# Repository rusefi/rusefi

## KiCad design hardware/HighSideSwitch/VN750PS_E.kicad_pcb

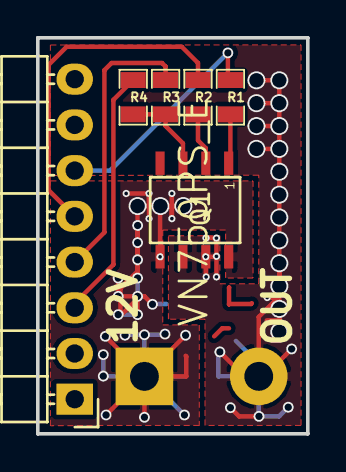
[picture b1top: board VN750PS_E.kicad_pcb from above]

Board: 4 copper layers, 15.0 x 22.0 mm, 8 parts (1 on the bottom side), 9 nets.

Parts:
D1: D; SM0805-diode
P1: CONN_01X08; Pin_Header_Angled_1x08
P2: CONN_01X02; Pin_Header_Straight_25x02
Q1: VN750PS_E; VN750PS-E
R1: 130; RES_0805
R2, R3, R4: 10k; RES_0805

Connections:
+5V: P1.3, R4.1
+12V: D1.1, P2.1, Q1.5, Q1.8
GND: P1.6, R1.1
unnamed: D1.2, P2.2, Q1.6, Q1.7
unnamed: P1.4, R3.1
unnamed: P1.5, R2.1
unnamed: Q1.1, R1.2
unnamed: Q1.2, R2.2
unnamed: Q1.3, R3.2, R4.2

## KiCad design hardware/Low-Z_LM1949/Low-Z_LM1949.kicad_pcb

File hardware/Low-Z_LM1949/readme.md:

https://rusefi.com/forum/viewtopic.php?f=4&t=431

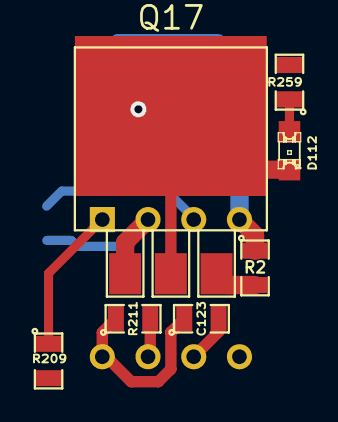
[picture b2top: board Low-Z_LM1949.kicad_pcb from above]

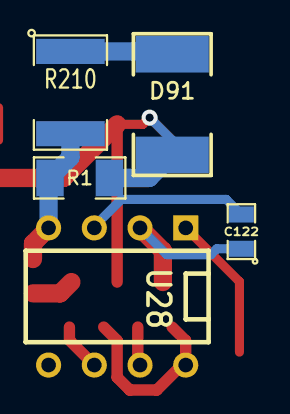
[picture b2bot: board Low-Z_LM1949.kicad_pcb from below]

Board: 2 copper layers, 12 parts (5 on the bottom side), 11 nets.

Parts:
C122: .01uF; SM0805
C123: 0.1uF; SM0805
D91: 33v 5w; SM2512
D112: LED; LED-0805
Q17: 2N6045; DPAK3
R1: 3.9k 1W; SM1206
R2: 2R; SM0805
R209: 1k; SM0805
R210: 0.1 2W; SM1812
R211: 39k; SM0805
R259: 3.3k; SM0805
U28: LM1949; DIP-8__300

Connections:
/5v_reg: R211.2, U28.7
/inductive_power_gnd: D91.1, R210.1, U28.5
/injector_output: D91.2, D112.2, Q17.2, R1.1
GND: C123.2, U28.6
unnamed: C122.1, Q17.1, U28.2
unnamed: C122.2, U28.3
unnamed: C123.1, R211.1, U28.8
unnamed: D112.1, R259.1
unnamed: Q17.3, R2.1, R210.2
unnamed: R1.2, R2.2, U28.4
unnamed: R209.1, U28.1

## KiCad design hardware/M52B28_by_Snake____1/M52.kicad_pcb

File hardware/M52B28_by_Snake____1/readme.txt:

https://rusefi.com/forum/viewtopic.php?f=3&t=1099

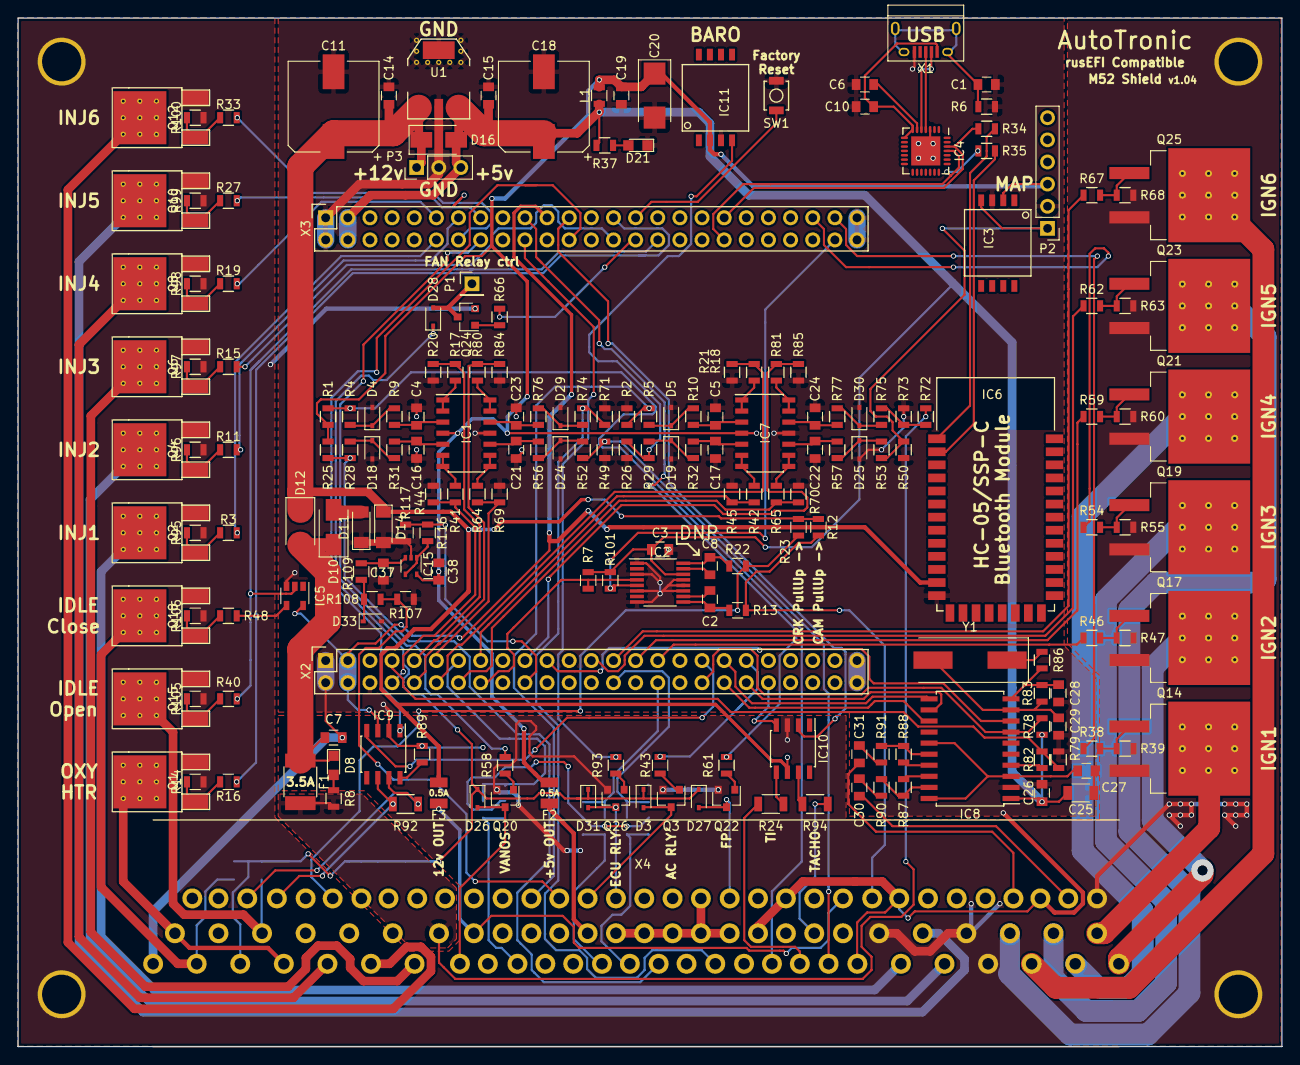
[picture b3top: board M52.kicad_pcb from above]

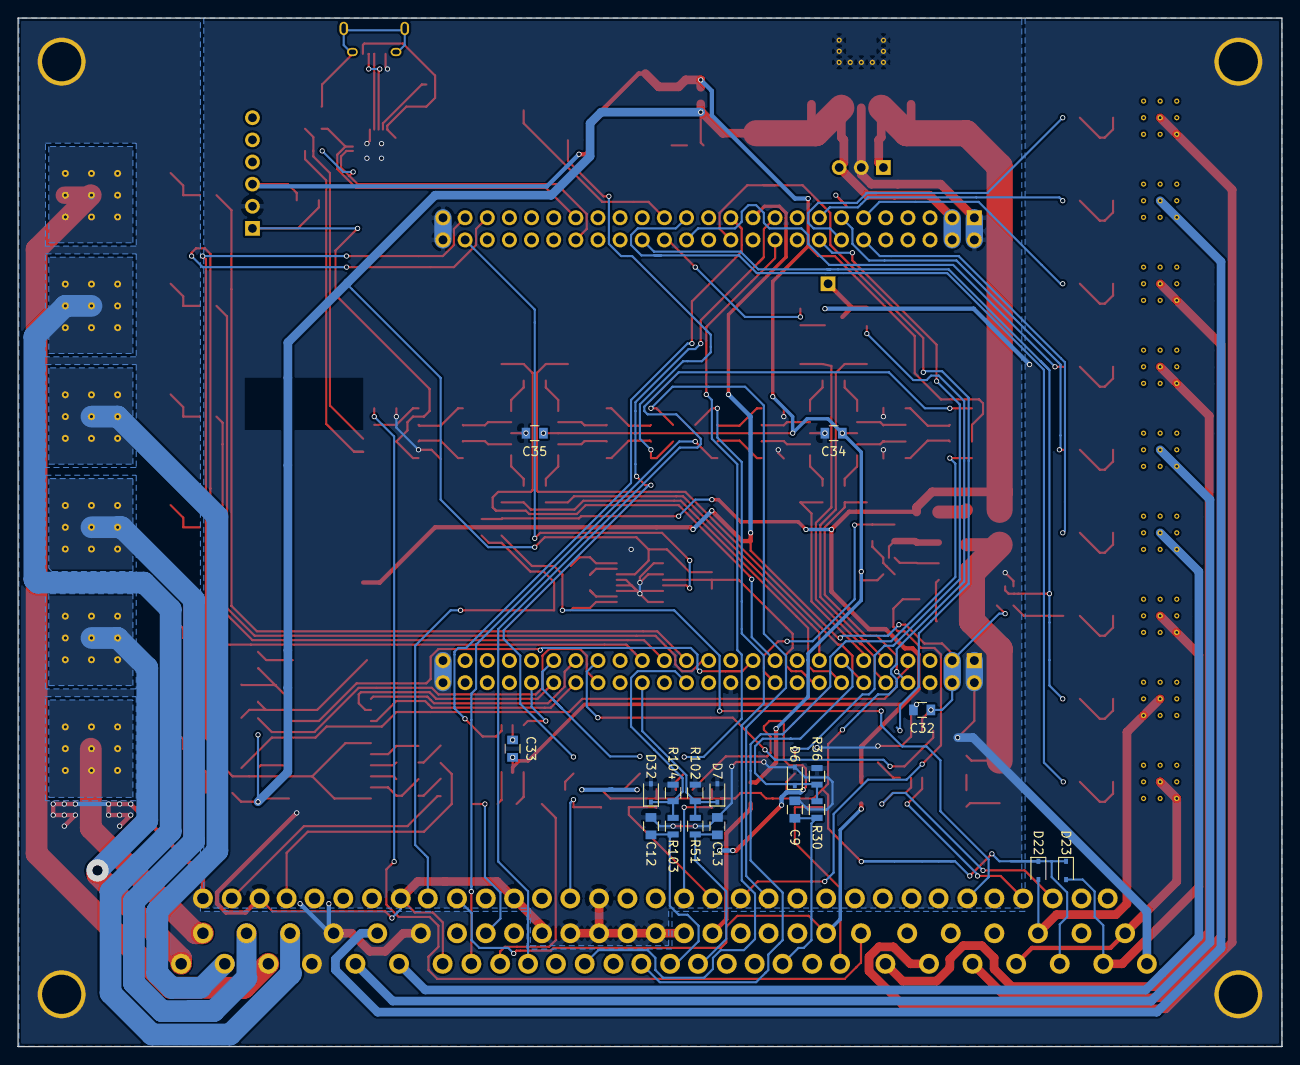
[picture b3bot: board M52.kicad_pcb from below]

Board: 2 copper layers, 145.0 x 118.0 mm, 220 parts (18 on the bottom side), 173 nets.

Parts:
C1, C3, C6, C10, C14, C15, C19, C26, C32, C33, C34, C35, C38: 100nF; C_0805
C2, C7, C8, C9: 1nF; C_0805
C4, C5, C12, C13, C16, C17, C21, C22, C23, C24, C37: 10nF; C_0805
C11, C18: 470uF; CP_Elec_10x10
C20: 10uF; CP_Tantalum_Case-C_EIA-6032-28_Reflow
C25: 4.7uF; C_1206
C27: 220nF; C_0805
C28, C29: 24pF; C_0805
C30, C31: 3.3nF; C_0805
D3, D22, D23, D26, D27, D28, D31: LL4148; D_SOD-323
D4, D5, D18, D19, D24, D25, D29, D30, D33: 5.1v; D_SOD-323
D6, D7, D32: 3.3v; D_SOD-323
D8: RED; LED_0805
D10, D16: LL4007; D_SMA_Standard
D11: 12v; D_MiniMELF
D12: SS34; D_SMA_Standard
D14: 22v; D_MiniMELF
D21: GREEN; LED_0805
F1: 3.5A; R_1812
F2, F3: 500mA; Fuse_SMD1206_Reflow
IC1, IC7: MCP6004; SOIC-14_3.9x8.7mm_Pitch1.27mm
IC2: MAX9926; QSOP-16_3.9x4.9mm_Pitch0.635mm
IC3, IC11: MPXH6400; MPXH6xxx
IC4: CP21xx; QFN-28-1EP_5x5mm_Pitch0.5mm
IC5: 74AHC1G14; SOT-23-5
IC6: HC-05
IC8: TPIC8101; SOIC-20W_7.5x12.8mm_Pitch1.27mm
IC9: SN65HVD230; SOIC-8_3.9x4.9mm_Pitch1.27mm
IC10: IX4424; SOIC-8_3.9x4.9mm_Pitch1.27mm
IC15: MCP6001; SOT-353_SC-70-5
L1: 1uH; R_0805
P1: FAN; Pin_Header_Straight_1x01_Pitch2.54mm
P2: MAP; Pin_Header_Straight_1x06_Pitch2.54mm
P3: CONN_01X03; Pin_Header_Straight_1x03_Pitch2.54mm
Q1, Q2, Q4, Q6, Q8, Q10, Q12, Q15, Q18: IRLR3103
Q3, Q20, Q22, Q24, Q26: MMBT2222A; SOT-23
Q14, Q17, Q19, Q21, Q23, Q25: NGD8201; TO-263-3LeadThermal
R1, R25, R30, R51, R103: 2.7K; R_0805
R2, R26, R49, R50, R71, R107: 500K; R_0805
R3, R11, R15, R16, R19, R27, R33, R34, R35, R36, R38, R40, R43, R46, R48, R54, R58, R59, R61, R62, R66, R67, R93, R102, R104: 1K; R_0805
R4, R5, R7, R8, R13, R22, R28, R29, R37, R52, R53, R73, R74, R75, R79, R82, R89, R101, R108: 10K; R_0805
R6, R14, R39, R47, R55, R60, R63, R68, R95, R96, R97, R98, R99, R100, R105, R106: 100K; R_0805
R9, R10, R31, R32, R56, R57, R76, R77, R109: 100R; R_0805
R12, R23: 4.7K; R_0805
R17, R18, R20, R21, R41, R42, R44, R45, R64, R65, R69, R70, R80, R81, R84, R85, R116, R117: 1.5K; R_0805
R24, R94: 22R; R_1206
R72: 50K; R_0805
R78: 5K; R_0805
R83: 2M; R_0805
R86: 820R; R_0805
R87, R88, R90, R91: 39K; R_0805
R92: 120R; R_1206
SW1: SW_Push; SW_SPST_B3U-1000P
U1: LM340MP-5.0; SOT-223Th.Relief
X1: USB_OTG; USB_Micro-B
X2, X3: CONN_02X25; Socket_Strip_Straight_2x25
X4: BOSCH_88PIN_02X44; BOSCH-88pin
Y1: 8MHz; Crystal_SMD_HC49-SD

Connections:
5vOUT: F2.1, X4.44
12vOUT: F3.1, X4.48, X4.65
+3V3: C32.1, IC5.5, IC6.12, IC9.3, X2.3, X2.4, X3.21
+5V: C3.2, C15.1, C18.1, C25.1, C26.1, D16.2, IC2.14, IC8.1, L1.1, P3.3, R7.2, R37.2, R78.2, R101.2, U1.3, X3.3, X3.4
+5VA: C19.1, C20.1, C34.1, C35.1, C38.1, F2.2, IC1.4, IC3.2, IC7.4, IC11.2, IC15.5, L1.2, P2.3, R1.1, R25.1
+12P: F1.2, R8.1, R72.1, X4.49
+12V: C11.1, C14.1, C33.2, D12.1, D14.1, D16.1, F3.2, IC10.6, P3.1, R12.1, R23.1, U1.1
AC: D3.2, Q3.3, X4.74
ACprSW: C13.1, R51.1, X4.16
ACreq: C9.1, R30.1, X4.19
BARO: IC11.4, R26.1, R29.1
BATT: D3.1, D22.1, D23.1, D26.1, D27.1, D28.1, D31.1, X4.26
CAM+: R12.2, R13.2, X4.64
CANH: IC9.7, R92.1, X4.86
CANL: IC9.6, R92.2, X4.85
CLT: R1.2, R4.1, X4.10
CRK: R22.2, R23.2, X4.83
ECU: D31.2, Q26.3, X4.73
FAN: D28.2, P1.1, Q24.3
FP: D27.2, Q22.3, X4.69
GND: C1.2, C3.1, C4.2, C5.2, C6.2, C7.2, C9.2, C10.2, C11.2, C12.2, C13.2, C14.2, C15.2, C16.2, C17.2, C18.2, C19.2, C20.2, C21.2, C22.2, C23.2, C24.2, C25.2, C26.2, C27.2, C28.1, C29.1, C32.2, C34.2, C35.2, C37.2, C38.2, D4.2, D5.2, D6.2, D7.2, D11.1, D14.2, D18.2, D19.2, D21.1, D24.2, D25.2, D29.2, D30.2, D32.2, D33.2, IC1.11, IC2.1, IC2.3, IC2.6, IC2.8, IC2.11, IC2.12, IC2.13, IC3.3, IC4.3, IC4.29, IC5.3, IC6.13, IC7.11, IC8.2, IC9.2, IC11.3, IC15.2, P2.2, P3.2, R2.2, R6.2, R20.2, R21.2, R26.2, R36.2, R44.2, R45.2, R49.2, R50.2, R69.2, R70.2, R71.2, R73.2, R79.1, R84.2, R85.2, R89.1, R102.2, R104.2, R107.2, R117.2, SW1.1, U1.2, X1.5, X2.1, X2.2, X2.6, X2.24, X2.49, X2.50, X3.1, X3.2, X3.49, X3.50, X4.7, X4.28, X4.38, X4.39, X4.40, X4.41, X4.42, X4.43, X4.58, X4.63, X4.67, X4.70
GNDPWR: C33.1, IC10.3, Q1.3, Q2.3, Q3.2, Q4.3, Q6.3, Q8.3, Q10.3, Q12.3, Q14.3, Q15.3, Q17.3, Q18.3, Q19.3, Q20.2, Q21.3, Q22.2, Q23.3, Q24.2, Q25.3, Q26.2, R14.2, R39.2, R47.2, R55.2, R60.2, R63.2, R68.2, R95.2, R96.2, R97.2, R98.2, R99.2, R100.2, R105.2, R106.2, X4.4, X4.32, X4.34, X4.56
IAT: R25.2, R28.1, X4.14
IDLc: D23.2, Q18.2, X4.27
IDLo: D22.2, Q15.2, X4.53
IGN1: Q14.2, X4.29
IGN2: Q17.2, X4.1
IGN3: Q19.2, X4.30
IGN4: Q21.2, X4.2
IGN5: Q23.2, X4.31
IGN6: Q25.2, X4.3
INJ1: Q2.2, X4.6
INJ2: Q4.2, X4.5
INJ3: Q6.2, X4.22
INJ4: Q8.2, X4.24
INJ5: Q10.2, X4.33
INJ6: Q12.2, X4.23
KNK1: C30.2, X4.57
KNK2: C31.1, X4.59
MAF: R49.1, R52.1, X4.8
MAP: IC3.4, P2.1, R50.1, R53.1
unnamed: C1.1, R6.1, X1.6
unnamed: C2.1, IC2.10
unnamed: C2.2, IC2.9, R13.1
unnamed: C4.1, IC1.3, R9.2
unnamed: C5.1, IC7.3, R10.2
unnamed: C6.1, IC4.6
unnamed: C7.1, D8.1, D10.1, D12.2, F1.1
unnamed: C8.1, IC2.16, R22.1
unnamed: C8.2, IC2.15
unnamed: C10.1, IC4.7, IC4.8, X1.1
unnamed: C16.1, IC1.5, R31.2
unnamed: C17.1, IC7.5, R32.2
unnamed: C21.1, IC1.10, R56.2
unnamed: C22.1, IC7.10, R57.2
unnamed: C23.1, IC1.12, R76.2
unnamed: C24.1, IC7.12, R77.2
unnamed: C27.1, IC8.3, IC8.15, IC8.20
unnamed: C28.2, IC8.10, R83.1, R86.1
unnamed: C29.2, IC8.9, R83.2, Y1.2
unnamed: C30.1, R90.2
unnamed: C31.2, R91.1
unnamed: C37.1, IC15.3, R109.2
unnamed: D4.1, R4.2, R9.1
unnamed: D5.1, R5.2, R10.1
unnamed: D8.2, R8.2
unnamed: D10.2, D11.2
unnamed: D18.1, R28.2, R31.1
unnamed: D19.1, R29.2, R32.1
unnamed: D21.2, R37.1
unnamed: D24.1, R52.2, R56.1
unnamed: D25.1, R53.2, R57.1
unnamed: D29.1, R74.2, R76.1
unnamed: D30.1, R75.2, R77.1
unnamed: D33.1, R108.2, R109.1
unnamed: IC1.1, IC1.2, R17.1
unnamed: IC1.6, IC1.7, R41.1
unnamed: IC1.8, IC1.9, R64.1
unnamed: IC1.13, IC1.14, R80.1
unnamed: IC4.4, X1.3
unnamed: IC4.5, X1.2
unnamed: IC5.4, R48.1
unnamed: IC6.1, R34.2
unnamed: IC6.2, R35.1
unnamed: IC7.1, IC7.2, R18.1
unnamed: IC7.6, IC7.7, R42.1
unnamed: IC7.8, IC7.9, R65.1
unnamed: IC7.13, IC7.14, R81.1
unnamed: IC8.4, R82.1
unnamed: IC8.16, R88.1, R91.2
unnamed: IC8.17, R88.2
unnamed: IC8.18, R87.1
unnamed: IC8.19, R87.2, R90.1
unnamed: IC9.8, R89.2
unnamed: IC10.5, R24.1
unnamed: IC10.7, R94.1
unnamed: IC15.1, IC15.4, R116.1
unnamed: Q1.1, R14.1, R16.2
unnamed: Q2.1, R3.2, R95.1
unnamed: Q3.1, R43.1
unnamed: Q4.1, R11.2, R96.1
unnamed: Q6.1, R15.2, R97.1
unnamed: Q8.1, R19.2, R98.1
unnamed: Q10.1, R27.2, R99.1
unnamed: Q12.1, R33.2, R100.1
unnamed: Q14.1, R38.2, R39.1
unnamed: Q15.1, R40.2, R105.1
unnamed: Q17.1, R46.2, R47.1
unnamed: Q18.1, R48.2, R106.1
unnamed: Q19.1, R54.2, R55.1
unnamed: Q20.1, R58.1
unnamed: Q21.1, R59.2, R60.1
unnamed: Q22.1, R61.1
unnamed: Q23.1, R62.2, R63.1
unnamed: Q24.1, R66.1
unnamed: Q25.1, R67.2, R68.1
unnamed: Q26.1, R93.1
unnamed: R72.2, R73.1, R75.1
unnamed: R86.2, Y1.1
OXY1: R107.1, R108.1, X4.75
OXY2: R2.1, R5.1, X4.76
OXYHTR: Q1.2, X4.25, X4.55
PA0: R64.2, R69.1, X2.11
PA1: R18.2, R21.1, X2.12
PA2: D6.1, R30.2, R36.1, X2.13
PA3: R65.2, R70.1, X2.14
PA4: R42.2, R45.1, X2.15
PA5: IC2.4, R7.1, X2.16
PB0: IC8.8, X2.21
PB3: R16.1, X3.27
PB6: IC9.1, X3.24
PB7: IC10.2, X3.23
PB8: R93.2, X3.20
PB9: R61.2, X3.19
PB11: IC8.7, R78.1, X2.36
PB12: IC9.4, X2.35
PB13: IC8.13, X2.38
PB14: IC8.11, X2.37
PB15: IC8.12, X2.40
PC0: R79.2, R82.2, X2.7
PC1: R41.2, R44.1, X2.8
PC2: R17.2, R20.1, X2.9
PC3: R80.2, R84.1, X2.10
PC4: R81.2, R85.1, X2.19
PC5: R116.2, R117.1, X2.20
PC6: IC2.5, R101.1, X3.48
PC7: R38.1, X3.47
PC9: R54.1, X3.45
PC10: IC4.25, R35.2, X3.38
PC11: IC4.26, R34.1, X3.37
PC13: R19.1, X3.11
PD3: IC5.2, R40.1, X3.32
PD5: R66.2, X3.30
PD6: SW1.2, X3.29
PD7: R15.1, X3.28
PD8: R43.2, X2.39
PD9: IC10.4, X2.42
PE2: R58.2, X3.16
PE3: R27.1, X3.15
PE4: R33.1, X3.14
PE5: R11.1, X3.13
PE6: R3.1, X3.12
PE8: R62.1, X2.25
PE9: D32.1, R103.2, R104.1, X2.28
PE10: R67.1, X2.27
PE12: R59.1, X2.29
PE13: D7.1, R51.2, R102.1, X2.32
PE14: R46.1, X2.31
RPM: R94.2, X4.36
TI: R24.2, X4.9
TPS: R71.1, R74.1, X4.12
VANOS: D26.2, Q20.3, X4.21
VSS: C12.1, R103.1, X4.15

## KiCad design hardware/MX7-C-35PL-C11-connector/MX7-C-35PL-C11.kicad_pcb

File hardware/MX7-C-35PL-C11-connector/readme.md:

35 pin connector Mazda NB2 Transmission Control Unit 

[Known issues](known_issues.txt)

https://rusefi.com/forum/viewtopic.php?f=4&t=1121

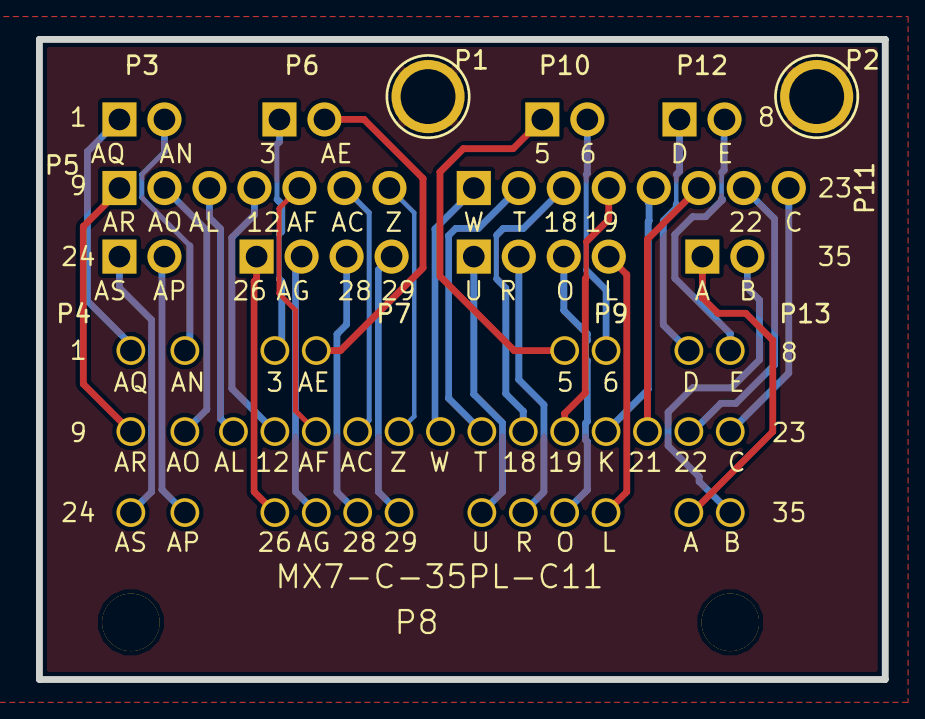
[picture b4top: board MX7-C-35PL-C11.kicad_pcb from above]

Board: 2 copper layers, 47.0 x 35.6 mm, 13 parts (0 on the bottom side), 36 nets.

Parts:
P1, P2: CONN_1; 1pin
P3, P4, P6, P10, P12, P13: CONN_01X02; Molex_NanoFit_1x02x2.50mm_Straight
P5: CONN_01X07; Molex_NanoFit_1x07x2.50mm_Straight
P7, P9: CONN_01X04; Molex_NanoFit_1x04x2.50mm_Straight
P8: MX7-C-35PL-C11
P11: CONN_01X08; Molex_NanoFit_1x08x2.50mm_Straight

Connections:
/3: P6.1, P8.3
/5: P8.5, P10.1
/6: P8.6, P10.2
/12: P5.4, P8.12
/18: P8.18, P11.3
/19: P8.19, P11.4
/21: P8.21, P11.6
/22: P8.22, P11.7
/26: P7.1, P8.26
/28: P7.3, P8.28
/29: P7.4, P8.29
/A: P8.34, P13.1
/AC: P5.6, P8.14
/AE: P6.2, P8.4
/AF: P5.5, P8.13
/AG: P7.2, P8.27
/AL: P5.3, P8.11
/AN: P3.2, P8.2
/AO: P5.2, P8.10
/AP: P4.2, P8.25
/AQ: P3.1, P8.1
/AR: P5.1, P8.9
/AS: P4.1, P8.24
/B: P8.35, P13.2
/C: P8.23, P11.8
/D: P8.7, P12.1
/F: P8.8, P12.2
/K: P8.20, P11.5
/L: P8.33, P9.4
/O: P8.32, P9.3
/R: P8.31, P9.2
/T: P8.17, P11.2
/U: P8.30, P9.1
/W: P8.16, P11.1
/Z: P5.7, P8.15
GND: P1.1, P2.1

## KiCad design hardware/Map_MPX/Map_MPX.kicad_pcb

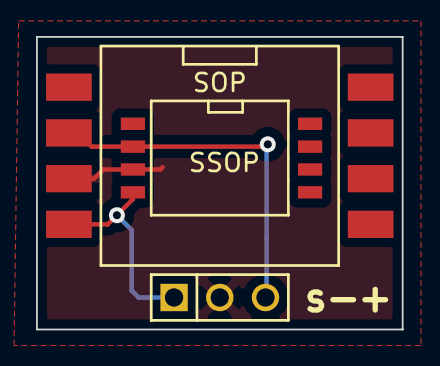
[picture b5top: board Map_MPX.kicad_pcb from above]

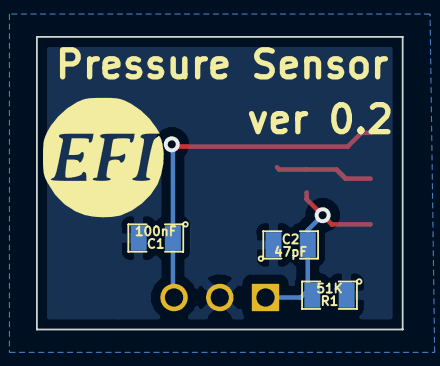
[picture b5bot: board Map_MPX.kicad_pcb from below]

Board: 2 copper layers, 20.3 x 16.3 mm, 4 parts (3 on the bottom side), 2 nets.

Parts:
C1: 100nF; SM0805
C2: 47pF; SM0805
R1: 51K; SM0805
SSOP: SOP; SSOP

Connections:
GND: C1.2, C2.1, R1.1
unnamed: C2.2, R1.2

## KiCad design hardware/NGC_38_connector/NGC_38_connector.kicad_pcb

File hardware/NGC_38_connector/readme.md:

38 pin Chrysler NGC connector

[3D printed case](3D_case)

https://rusefi.com/forum/viewtopic.php?f=4&t=764

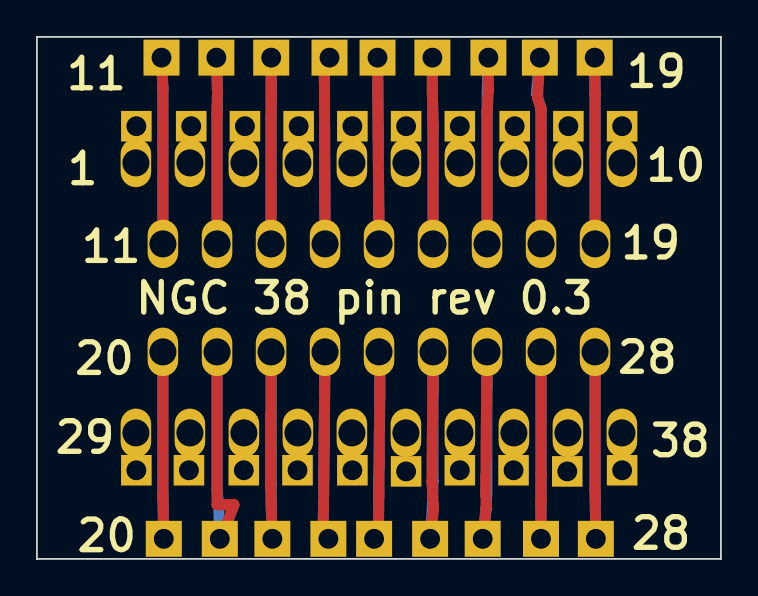
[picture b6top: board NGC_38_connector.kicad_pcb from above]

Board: 2 copper layers, 38.0 x 29.0 mm, 5 parts (0 on the bottom side), 38 nets.

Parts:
P1: DIL38; PCM_C1
P2, P4: CONN_10; SIL-10
P3, P5: CONN_9; SIL-9

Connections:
unnamed: P1.15, P3.5
unnamed: P1.10, P2.10
unnamed: P1.9, P2.9
unnamed: P1.8, P2.8
unnamed: P1.7, P2.7
unnamed: P1.6, P2.6
unnamed: P1.5, P2.5
unnamed: P1.4, P2.4
unnamed: P1.3, P2.3
unnamed: P1.2, P2.2
unnamed: P1.1, P2.1
unnamed: P1.19, P3.9
unnamed: P1.18, P3.8
unnamed: P1.17, P3.7
unnamed: P1.16, P3.6
unnamed: P1.20, P5.1
unnamed: P1.14, P3.4
unnamed: P1.13, P3.3
unnamed: P1.12, P3.2
unnamed: P1.11, P3.1
unnamed: P1.28, P5.9
unnamed: P1.27, P5.8
unnamed: P1.26, P5.7
unnamed: P1.25, P5.6
unnamed: P1.24, P5.5
unnamed: P1.23, P5.4
unnamed: P1.22, P5.3
unnamed: P1.21, P5.2
unnamed: P1.31, P4.3
unnamed: P1.34, P4.6
unnamed: P1.33, P4.5
unnamed: P1.32, P4.4
unnamed: P1.38, P4.10
unnamed: P1.30, P4.2
unnamed: P1.29, P4.1
unnamed: P1.37, P4.9
unnamed: P1.36, P4.8
unnamed: P1.35, P4.7

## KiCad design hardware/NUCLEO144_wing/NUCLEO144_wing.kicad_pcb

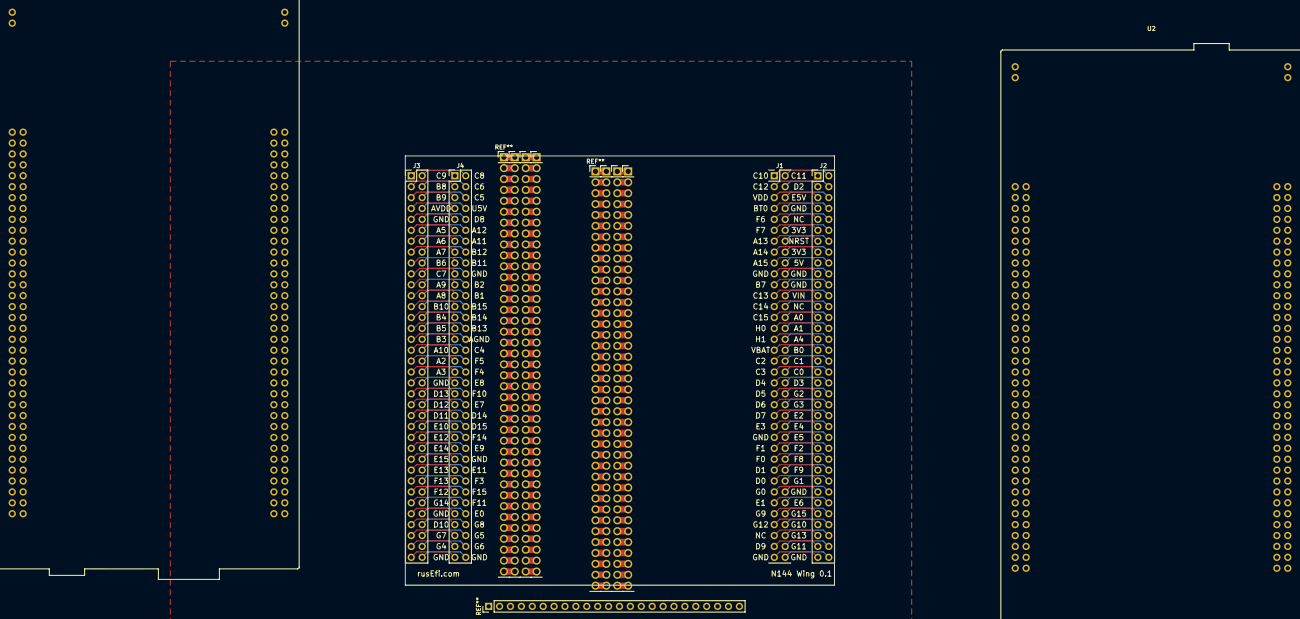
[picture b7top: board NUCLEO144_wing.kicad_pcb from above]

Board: 2 copper layers, 100.0 x 100.0 mm, 6 parts (0 on the bottom side), 144 nets.

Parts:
J1, J2, J3, J4: Conn_02x36_Top_Bottom; Pin_Header_Straight_2x36_Pitch2.54mm
U1, U2: NUCLEO144-F429ZI; ST_Morpho_Connector_144_STLink

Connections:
unnamed: J1.1, J2.1
unnamed: J1.2, J2.2
unnamed: J1.3, J2.3
unnamed: J1.4, J2.4
unnamed: J1.5, J2.5
unnamed: J1.6, J2.6
unnamed: J1.7, J2.7
unnamed: J1.8, J2.8
unnamed: J1.9, J2.9
unnamed: J1.10, J2.10
unnamed: J1.11, J2.11
unnamed: J1.12, J2.12
unnamed: J1.13, J2.13
unnamed: J1.14, J2.14
unnamed: J1.15, J2.15
unnamed: J1.16, J2.16
unnamed: J1.17, J2.17
unnamed: J1.18, J2.18
unnamed: J1.19, J2.19
unnamed: J1.20, J2.20
unnamed: J1.21, J2.21
unnamed: J1.22, J2.22
unnamed: J1.23, J2.23
unnamed: J1.24, J2.24
unnamed: J1.25, J2.25
unnamed: J1.26, J2.26
unnamed: J1.27, J2.27
unnamed: J1.28, J2.28
unnamed: J1.29, J2.29
unnamed: J1.30, J2.30
unnamed: J1.31, J2.31
unnamed: J1.32, J2.32
unnamed: J1.33, J2.33
unnamed: J1.34, J2.34
unnamed: J1.35, J2.35
unnamed: J1.36, J2.36
unnamed: J1.37, J2.37
unnamed: J1.38, J2.38
unnamed: J1.39, J2.39
unnamed: J1.40, J2.40
unnamed: J1.41, J2.41
unnamed: J1.42, J2.42
unnamed: J1.43, J2.43
unnamed: J1.44, J2.44
unnamed: J1.45, J2.45
unnamed: J1.46, J2.46
unnamed: J1.47, J2.47
unnamed: J1.48, J2.48
unnamed: J1.49, J2.49
unnamed: J1.50, J2.50
unnamed: J1.51, J2.51
unnamed: J1.52, J2.52
unnamed: J1.53, J2.53
unnamed: J1.54, J2.54
unnamed: J1.55, J2.55
unnamed: J1.56, J2.56
unnamed: J1.57, J2.57
unnamed: J1.58, J2.58
unnamed: J1.59, J2.59
unnamed: J1.60, J2.60
unnamed: J1.61, J2.61
unnamed: J1.62, J2.62
unnamed: J1.63, J2.63
unnamed: J1.64, J2.64
unnamed: J1.65, J2.65
unnamed: J1.66, J2.66
unnamed: J1.67, J2.67
unnamed: J1.68, J2.68
unnamed: J1.69, J2.69
unnamed: J1.70, J2.70
unnamed: J1.71, J2.71
unnamed: J1.72, J2.72
unnamed: J3.1, J4.1
unnamed: J3.2, J4.2
unnamed: J3.3, J4.3
unnamed: J3.4, J4.4
unnamed: J3.5, J4.5
unnamed: J3.6, J4.6
unnamed: J3.7, J4.7
unnamed: J3.8, J4.8
unnamed: J3.9, J4.9
unnamed: J3.10, J4.10
unnamed: J3.11, J4.11
unnamed: J3.12, J4.12
unnamed: J3.13, J4.13
unnamed: J3.14, J4.14
unnamed: J3.15, J4.15
unnamed: J3.16, J4.16
unnamed: J3.17, J4.17
unnamed: J3.18, J4.18
unnamed: J3.19, J4.19
unnamed: J3.20, J4.20
unnamed: J3.21, J4.21
unnamed: J3.22, J4.22
unnamed: J3.23, J4.23
unnamed: J3.24, J4.24
unnamed: J3.25, J4.25
unnamed: J3.26, J4.26
unnamed: J3.27, J4.27
unnamed: J3.28, J4.28
unnamed: J3.29, J4.29
unnamed: J3.30, J4.30
unnamed: J3.31, J4.31
unnamed: J3.32, J4.32
unnamed: J3.33, J4.33
unnamed: J3.34, J4.34
unnamed: J3.35, J4.35
unnamed: J3.36, J4.36
unnamed: J3.37, J4.37
unnamed: J3.38, J4.38
unnamed: J3.39, J4.39
unnamed: J3.40, J4.40
unnamed: J3.41, J4.41
unnamed: J3.42, J4.42
unnamed: J3.43, J4.43
unnamed: J3.44, J4.44
unnamed: J3.45, J4.45
unnamed: J3.46, J4.46
unnamed: J3.47, J4.47
unnamed: J3.48, J4.48
unnamed: J3.49, J4.49
unnamed: J3.50, J4.50
unnamed: J3.51, J4.51
unnamed: J3.52, J4.52
unnamed: J3.53, J4.53
unnamed: J3.54, J4.54
unnamed: J3.55, J4.55
unnamed: J3.56, J4.56
unnamed: J3.57, J4.57
unnamed: J3.58, J4.58
unnamed: J3.59, J4.59
unnamed: J3.60, J4.60
unnamed: J3.61, J4.61
unnamed: J3.62, J4.62
unnamed: J3.63, J4.63
unnamed: J3.64, J4.64
unnamed: J3.65, J4.65
unnamed: J3.66, J4.66
unnamed: J3.67, J4.67
unnamed: J3.68, J4.68
unnamed: J3.69, J4.69
unnamed: J3.70, J4.70
unnamed: J3.71, J4.71
unnamed: J3.72, J4.72

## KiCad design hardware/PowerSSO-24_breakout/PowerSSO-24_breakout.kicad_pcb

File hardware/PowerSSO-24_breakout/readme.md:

https://rusefi.com/forum/viewtopic.php?f=4&t=747&p=13402#p13402

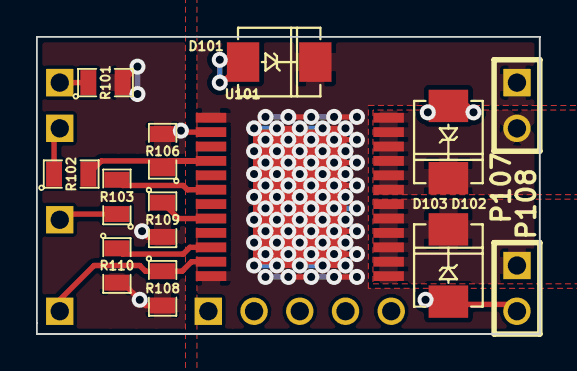
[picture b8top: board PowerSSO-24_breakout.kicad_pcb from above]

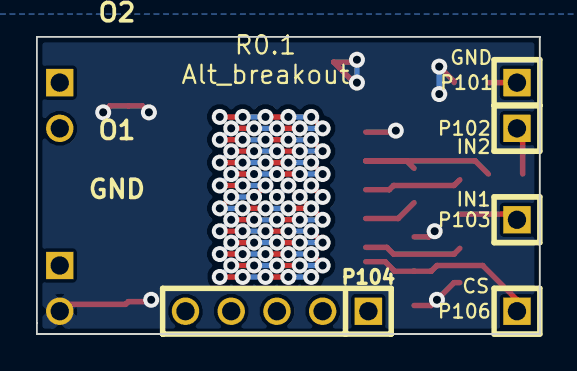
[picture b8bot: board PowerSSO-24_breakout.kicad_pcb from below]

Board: 2 copper layers, 27.9 x 16.5 mm, 18 parts (5 on the bottom side), 12 nets.

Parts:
D101, D102, D103: P6SMB36AT3G; DO-214AA(SMB)
P101, P102, P103, P106: CONN_1; SIL-1
P104: CONN_5; SIL-5
P107, P108: CONN_2; SIL-2
R101: TBD; SM0805
R102, R103, R106, R108: 10K; SM0805
R109, R110: 1K; SM0805
U101: VND5E025AKTR; PowerSSO-24

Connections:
/CS_DIS: P106.1, R108.1, U101.11
/I1: R109.1, U101.8
/I2: R110.1, U101.10
/IN1: R103.2, U101.6
/IN2: R102.2, R106.1, U101.4
/O1: D103.2, P108.1, U101.13, U101.14, U101.15, U101.16, U101.17, U101.18
/O2: D102.2, P107.2, U101.19, U101.20, U101.21, U101.22, U101.23, U101.24
/VCC: D101.2, P107.1, U101.1, U101.12, U101.EXP
GND: D101.1, D102.1, D103.1, P108.2, R101.2, R106.2, R108.2, R109.2, R110.2, U101.2
unnamed: P101.1, R101.1
unnamed: P103.1, R103.1
unnamed: P102.1, R102.1
